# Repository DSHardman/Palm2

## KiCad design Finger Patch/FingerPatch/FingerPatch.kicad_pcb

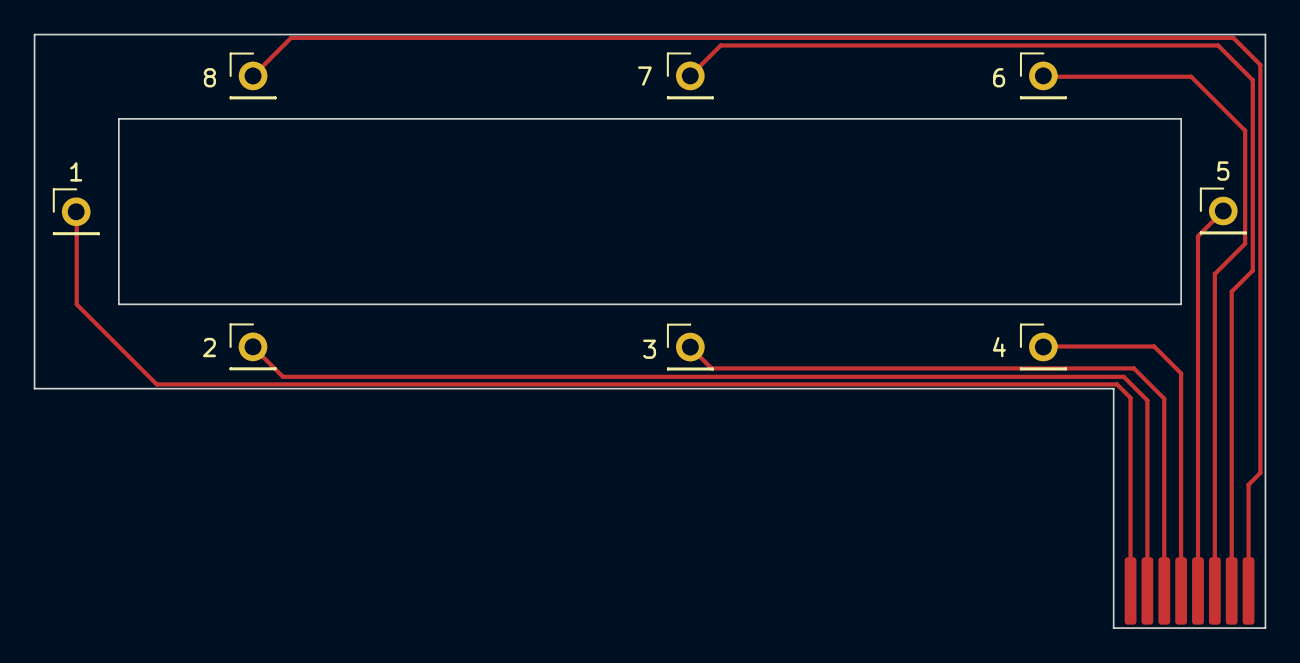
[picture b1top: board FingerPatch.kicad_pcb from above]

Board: 2 copper layers, 73.0 x 35.2 mm, 9 parts (0 on the bottom side), 8 nets.

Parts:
1, 2, 3, 4, 5, 6, 7, 8: Conn_01x01_Pin; PinHeader_1x01_P2.54mm_Vertical
J1: Conn_01x08_Pin; FFC8End

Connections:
unnamed: 1.1, J1.1
unnamed: 2.1, J1.2
unnamed: 3.1, J1.3
unnamed: 4.1, J1.4
unnamed: 5.1, J1.5
unnamed: 6.1, J1.6
unnamed: 7.1, J1.7
unnamed: 8.1, J1.8

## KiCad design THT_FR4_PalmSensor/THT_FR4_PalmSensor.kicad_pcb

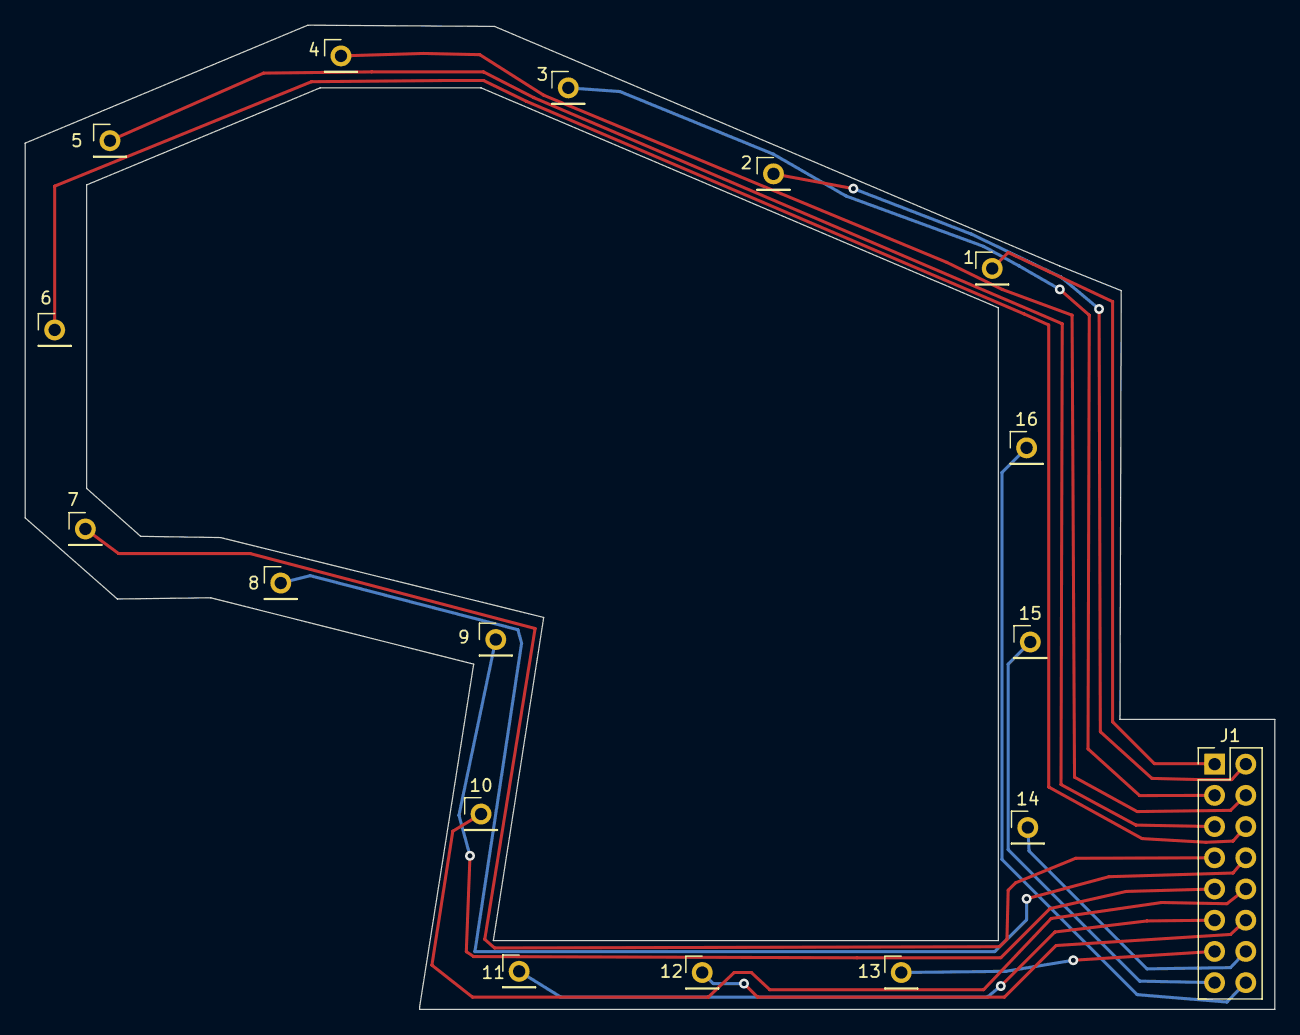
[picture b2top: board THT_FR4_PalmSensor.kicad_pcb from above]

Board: 2 copper layers, 101.7 x 80.1 mm, 17 parts (0 on the bottom side), 16 nets.

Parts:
1, 2, 3, 4, 5, 6, 7, 8, 9, 10, 11, 12, 13, 14, 15, 16: TestPoint; PinHeader_1x01_P2.54mm_Vertical
J1: Conn_01x16_Pin; PinHeader_2x08_P2.54mm_Vertical

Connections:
unnamed: 1.1, J1.1
unnamed: 2.1, J1.2
unnamed: 3.1, J1.3
unnamed: 4.1, J1.4
unnamed: 5.1, J1.5
unnamed: 6.1, J1.6
unnamed: 7.1, J1.7
unnamed: 8.1, J1.8
unnamed: 9.1, J1.9
unnamed: 10.1, J1.10
unnamed: 11.1, J1.11
unnamed: 12.1, J1.12
unnamed: 13.1, J1.13
unnamed: 14.1, J1.14
unnamed: 15.1, J1.15
unnamed: 16.1, J1.16
